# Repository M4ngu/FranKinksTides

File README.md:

# FranKinksTides
cc-by-sa original     design by Émile Gillet

https://www.tesseractmodular.com/eurorack-modules/frankinkstides-1-2

Dual Tidal Modulator - Eurorack Module

FranKinksTides is a eurorack module with 2 tidal modulators based on MI Tides1 (by Émilie Gillet) and the Swirls PCB layout  (by Electric Mist)

https://mutable-instruments.net/modules/tides1/

The central part is a mixer for the 2 signals and the Max/Min circuit from MI Kinks 

https://mutable-instruments.net/modules/kinks/

It can be a dual function generator, a complex oscillator or any other combination of VCO, LFO, ENV

version history:

## first version

-First working version of this kind of 'digital Maths'

## second version (v1.2):

-Mix output is now buffered, no signal bleeding on single outs.

-Mix pot controls also the balance of the signals sent to the max/min circuit.

-Uni/bi switch now also determines the signal sent to FM1.

-Clock/sync switch has now a center OFF position, no need of plugging a dummy cable in the Clock1 when using Sheeps firmware to avoid ultra fast sound bank changes. 

other small improvements for DIY:

-Bigger font size on the pcb.

-Parts renumbered for easy DIY.

## last version (v1.4):

-Added resistors to make the Balance pot exponential, so center position has a louder output.

-PCB modified with the Thonkiccon recommendation (with no ground plane / traces under the jacks)

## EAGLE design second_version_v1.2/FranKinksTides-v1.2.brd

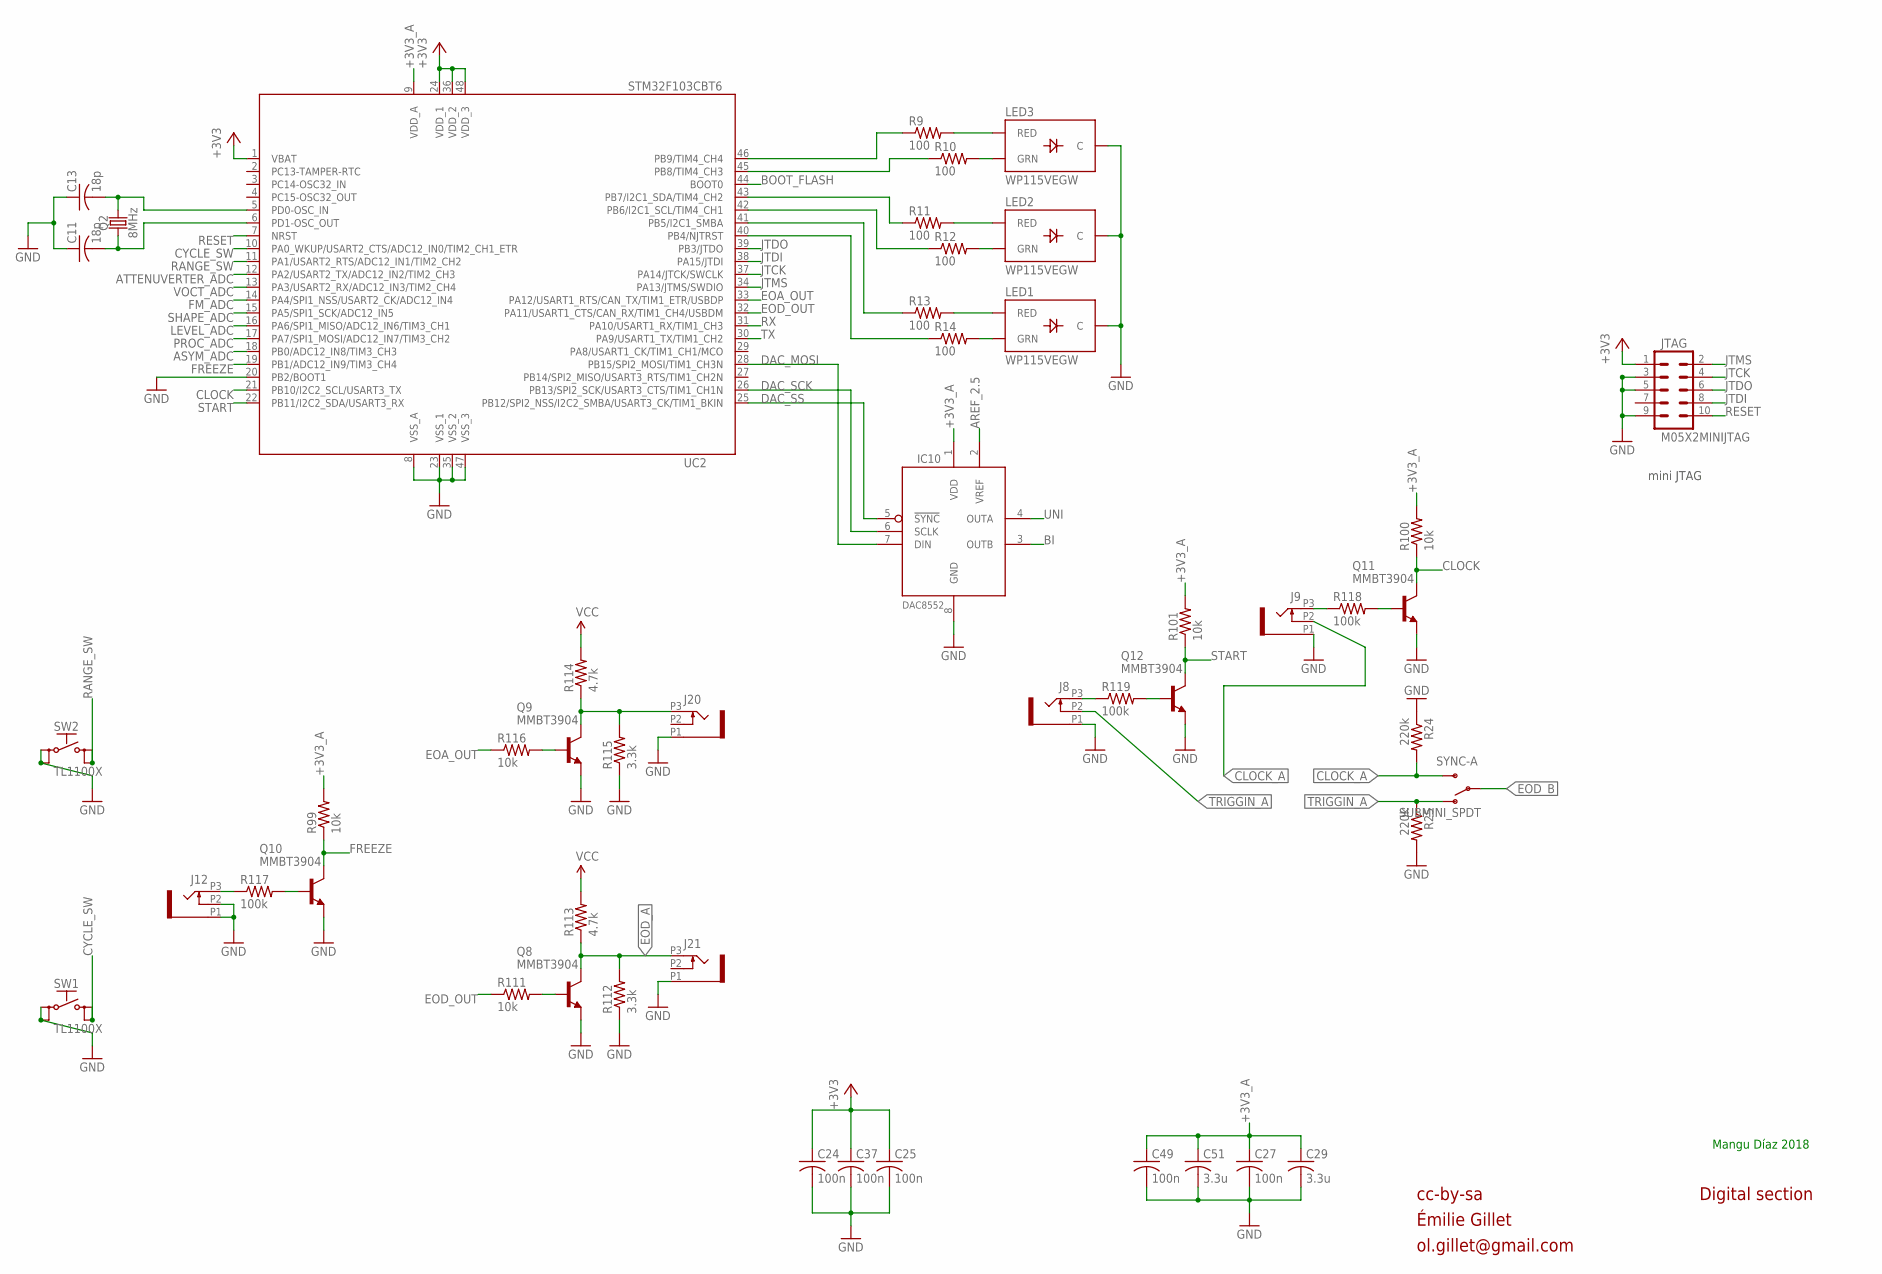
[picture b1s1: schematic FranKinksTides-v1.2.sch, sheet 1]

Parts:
C11, C13: 18p; C0603
C24, C25, C27, C37, C49: 100n; C0603
C29, C51: 3.3u; C0603
IC10: DAC8552; MSOP-8
J8, J9, J12, J20, J21: PJ301_GUI6; OG-PJ301_VARIATIONS_WQP_PJ_301M6
JTAG: M05X2MINIJTAG; 2X5-1.27
LED1, LED2, LED3: WP115VEGW; LED-BICOLOR-THROUGHHOLE
Q2: 8MHz; HC49UP
Q8, Q9, Q10, Q11, Q12: MMBT3904; SOT23-BEC
R9, R10, R11, R12, R13, R14: 100; R0603
R24, R25: 220k; R0603
R99, R100, R101, R111, R116: 10k; R0603
R112, R115: 3.3k; R0603
R113, R114: 4.7k; R0603
R117, R118, R119: 100k; R0603
SW1, SW2: TL1100X
SYNC-A: SUBMINI_SPDT; SUBMINI_TOGGLE
UC2: STM32F103CBT6; LQFP48

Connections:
+3V3: C24.1, C25.1, C37.1, JTAG.1, UC2.1 (VBAT), UC2.24 (VDD_1), UC2.36 (VDD_2), UC2.48 (VDD_3); also elsewhere on the board
+3V3_A: C27.1, C29.1, C49.1, C51.1, IC10.1 (VDD), R99.2, R100.2, R101.2, UC2.9 (VDD_A); also elsewhere on the board
AREF_2.5: IC10.2 (VREF); also elsewhere on the board
ASYM_ADC: UC2.18 (PB0/ADC12_IN8/TIM3_CH3); also elsewhere on the board
ATTENUVERTER_ADC: UC2.12 (PA2/USART2_TX/ADC12_IN2/TIM2_CH3); also elsewhere on the board
BI: IC10.3 (OUTB); also elsewhere on the board
BOOT_FLASH: UC2.44 (BOOT0); also elsewhere on the board
CLOCK: Q11.C, R100.1, UC2.21 (PB10/I2C2_SCL/USART3_TX); also elsewhere on the board
CLOCK_A: J9.P2 (2), R24.2, SYNC-A.3 (S)
CYCLE_SW: SW1.3 (S), SW1.4 (S1), UC2.10 (PA0_WKUP/USART2_CTS/ADC12_IN0/TIM2_CH1_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); also elsewhere on the board
DAC_MOSI: IC10.7 (DIN), UC2.28 (PB15/SPI2_MOSI/TIM1_CH3N); also elsewhere on the board
DAC_SCK: IC10.6 (SCLK), UC2.26 (PB13/SPI2_SCK/USART3_CTS/TIM1_CH1N); also elsewhere on the board
DAC_SS: IC10.5 (!SYNC), UC2.25 (PB12/SPI2_NSS/I2C2_SMBA/USART3_CK/TIM1_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); also elsewhere on the board
EOA_OUT: R116.1, UC2.33 (PA12/USART1_RTS/CAN_TX/TIM1_ETR/USBDP); also elsewhere on the board
EOD_A: J21.P3 (3), Q8.C, R112.2, R113.1; also elsewhere on the board
EOD_B: SYNC-A.COM (COMMON); also elsewhere on the board
EOD_OUT: R111.1, UC2.32 (PA11/USART1_CTS/CAN_RX/TIM1_CH4/USBDM); also elsewhere on the board
FM_ADC: UC2.14 (PA4/SPI1_NSS/USART2_CK/ADC12_IN4); also elsewhere on the board
FREEZE: Q10.C, R99.1, UC2.19 (PB1/ADC12_IN9/TIM3_CH4); also elsewhere on the board
GND: C11.1, C13.1, C24.2, C25.2, C27.2, C29.2, C37.2, C49.2, C51.2, IC10.8 (GND), J8.P1 (1), J9.P1 (1), J12.P1 (1), J12.P2 (2), J20.P1 (1), J21.P1 (1), JTAG.3, JTAG.5, JTAG.9, LED1.2 (C), LED2.2 (C), LED3.2 (C), Q8.E, Q9.E, Q10.E, Q11.E, Q12.E, R24.1, R25.2, R112.1, R115.1, SW1.1, SW1.2 (P1), SW2.1, SW2.2 (P1), UC2.8 (VSS_A), UC2.20 (PB2/BOOT1), UC2.23 (VSS_1), UC2.35 (VSS_2), UC2.47 (VSS_3); also elsewhere on the board
JTCK: JTAG.4, UC2.37 (PA14/JTCK/SWCLK); also elsewhere on the board
JTDI: JTAG.8, UC2.38 (PA15/JTDI); also elsewhere on the board
JTDO: JTAG.6, UC2.39 (PB3/JTDO); also elsewhere on the board
JTMS: JTAG.2, UC2.34 (PA13/JTMS/SWDIO); also elsewhere on the board
LEVEL_ADC: UC2.16 (PA6/SPI1_MISO/ADC12_IN6/TIM3_CH1); also elsewhere on the board
unnamed: C13.2, Q2.2, UC2.5 (PD0-OSC_IN)
unnamed: C11.2, Q2.1, UC2.6 (PD1-OSC_OUT)
unnamed: J8.P3 (3), R119.1
unnamed: J12.P3 (3), R117.1
unnamed: Q10.B, R117.2
unnamed: J9.P3 (3), R118.1
unnamed: Q11.B, R118.2
unnamed: Q8.B, R111.2
unnamed: LED3.3 (RED), R9.2
unnamed: LED3.1 (GRN), R10.2
unnamed: LED2.3 (RED), R11.2
unnamed: LED2.1 (GRN), R12.2
unnamed: LED1.3 (RED), R13.2
unnamed: LED1.1 (GRN), R14.2
unnamed: R9.1, UC2.46 (PB9/TIM4_CH4)
unnamed: R10.1, UC2.45 (PB8/TIM4_CH3)
unnamed: R11.1, UC2.43 (PB7/I2C1_SDA/TIM4_CH2)
unnamed: R12.1, UC2.42 (PB6/I2C1_SCL/TIM4_CH1)
unnamed: R13.1, UC2.41 (PB5/I2C1_SMBA)
unnamed: R14.1, UC2.40 (PB4/NJTRST)
unnamed: J20.P3 (3), Q9.C, R114.1, R115.2
unnamed: Q9.B, R116.2
unnamed: Q12.B, R119.2
PROC_ADC: UC2.17 (PA7/SPI1_MOSI/ADC12_IN7/TIM3_CH2); also elsewhere on the board
RANGE_SW: SW2.3 (S), SW2.4 (S1), UC2.11 (PA1/USART2_RTS/ADC12_IN1/TIM2_CH2); also elsewhere on the board
RESET: JTAG.10, UC2.7 (NRST); also elsewhere on the board
RX: UC2.31 (PA10/USART1_RX/TIM1_CH3); also elsewhere on the board
SHAPE_ADC: UC2.15 (PA5/SPI1_SCK/ADC12_IN5); also elsewhere on the board
START: Q12.C, R101.1, UC2.22 (PB11/I2C2_SDA/USART3_RX); also elsewhere on the board
TRIGGIN_A: J8.P2 (2), R25.1, SYNC-A.1 (O)
TX: UC2.30 (PA9/USART1_TX/TIM1_CH2); also elsewhere on the board
UNI: IC10.4 (OUTA); also elsewhere on the board
VCC: R113.2, R114.2; also elsewhere on the board
VOCT_ADC: UC2.13 (PA3/USART2_RX/ADC12_IN3/TIM2_CH4); also elsewhere on the board

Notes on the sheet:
cc-by-sa
Émilie Gillet
ol.gillet@gmail.com
Digital section
mini JTAG
Mangu Díaz 2018

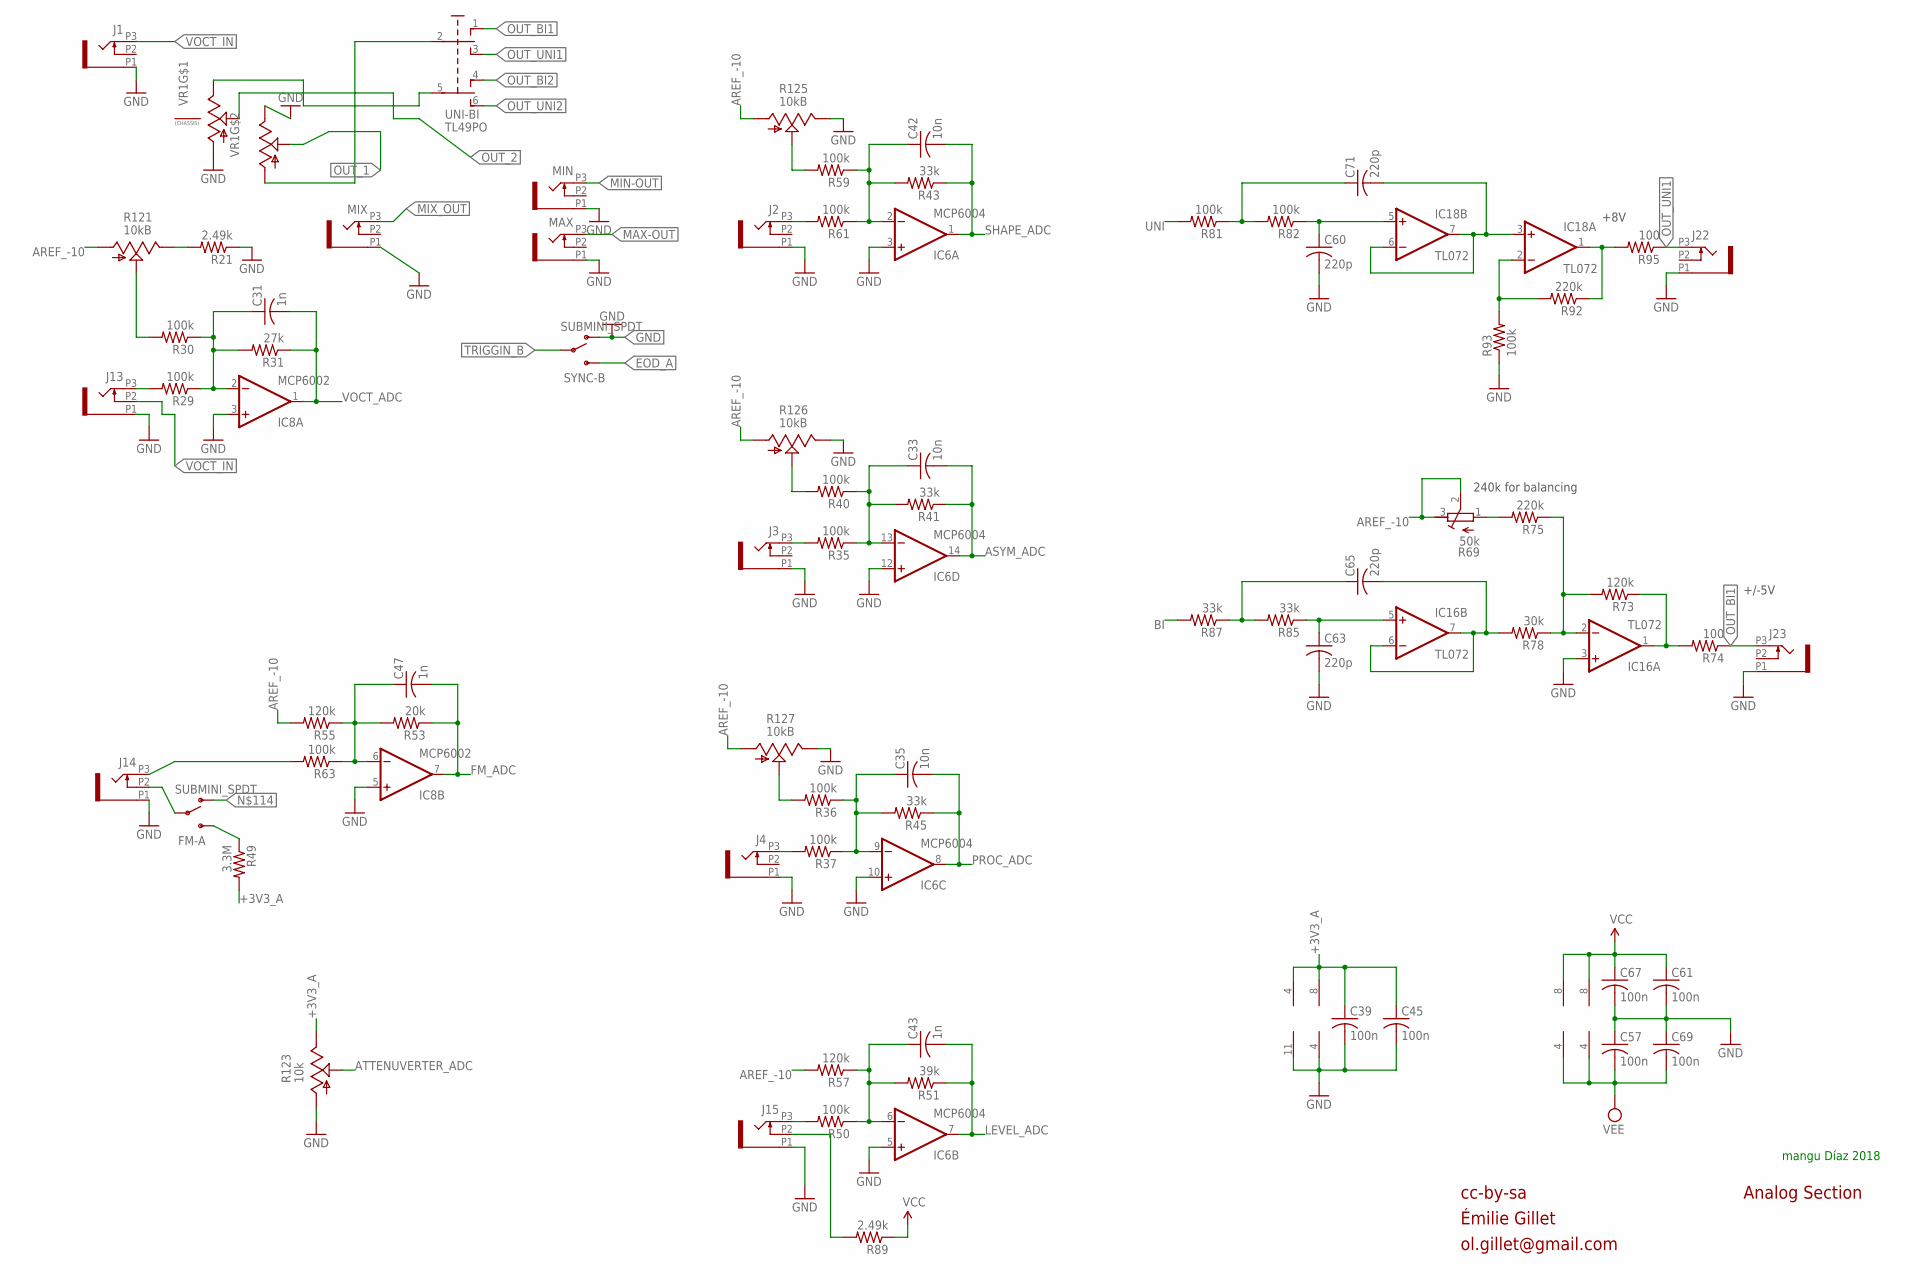
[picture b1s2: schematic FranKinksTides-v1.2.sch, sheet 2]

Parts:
C31, C43, C47: 1n; C0603
C33, C35, C42: 10n; C0603
C39, C45, C57, C61, C67, C69: 100n; C0603
C60, C63, C65, C71: 220p; C0603
FM-A: SUBMINI_SPDT; SUBMINI_TOGGLE
IC6: MCP6004; TSSOP14
IC8: MCP6002; SO08
IC16, IC18: TL072; TSSOP-8
J1, J2, J3, J4, J13, J14, J15, J22, J23: PJ301_GUI6; OG-PJ301_VARIATIONS_WQP_PJ_301M6
MAX: PJ301_GUI6; OG-PJ301_VARIATIONS_WQP_PJ_301M6
MIN: PJ301_GUI6; OG-PJ301_VARIATIONS_WQP_PJ_301M6
MIX: PJ301_GUI6; OG-PJ301_VARIATIONS_WQP_PJ_301M6
R21: 2.49k; R0603
R29, R30, R35, R36, R37, R40, R50, R59, R61, R63, R81, R82, R93: 100k; R0603
R31: 27k; R0603
R41, R43, R45, R85, R87: 33k; R0603
R49: 3.3M; R0603
R51: 39k; R0603
R53: 20k; R0603
R55, R57, R73: 120k; R0603
R69: 50k; RTRIM3296W
R74, R95: 100; R0603
R75, R92: 220k; R0603
R78: 30k; R0603
R89: 2.49k; R0805
R121: 10kB; ALPS_POT_VERTICAL_PS
R123: 10k; TALLTRIMMER
R125, R126, R127: 10kB; TALLTRIMMER
SYNC-B: SUBMINI_SPDT; SUBMINI_TOGGLE
UNI-BI: TL49PO; TL4XPO
VR1: ALPHA-9MM-DUALPOT; DUAL_9MM_SNAP-IN_POT

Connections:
+3V3_A: C39.1, C45.1, IC6.4 (V+), IC8.8 (V+), R49.2, R123.P$1 (E); also elsewhere on the board
AREF_-10: R55.2, R57.2, R69.2 (S), R69.3 (E), R121.P$3 (A), R125.P$3 (A), R126.P$3 (A), R127.P$3 (A); also elsewhere on the board
ASYM_ADC: C33.2, IC6.14 (OUT), R41.1; also elsewhere on the board
ATTENUVERTER_ADC: R123.P$2 (S); also elsewhere on the board
BI: R87.2; also elsewhere on the board
BI_OUT: IC16.1 (OUT), R73.1, R74.2
EOD_A: SYNC-B.3 (S); also elsewhere on the board
FM_ADC: C47.2, IC8.7 (OUT), R53.1; also elsewhere on the board
F_CV: IC16.2 (-IN), R73.2, R75.1, R78.1
GND: C39.2, C45.2, C57.1, C60.2, C61.2, C63.2, C67.2, C69.1, IC6.3 (+IN), IC6.5 (+IN), IC6.10 (+IN), IC6.11 (V-), IC6.12 (+IN), IC8.3 (+IN), IC8.4 (V-), IC8.5 (+IN), IC16.3 (+IN), J1.P1 (1), J2.P1 (1), J3.P1 (1), J4.P1 (1), J13.P1 (1), J14.P1 (1), J15.P1 (1), J22.P1 (1), J23.P1 (1), MAX.P1 (1), MIN.P1 (1), MIX.P1 (1), R21.1, R93.1, R123.P$3 (A), R125.P$1 (E), R126.P$1 (E), R127.P$1 (E), SYNC-B.1 (O), VR1.1 (A), VR1.3B (E); also elsewhere on the board
LEVEL_ADC: C43.2, IC6.7 (OUT), R51.1; also elsewhere on the board
MAX-OUT: MAX.P3 (3); also elsewhere on the board
MIN-OUT: MIN.P3 (3); also elsewhere on the board
MIX_OUT: MIX.P3 (3); also elsewhere on the board
unnamed: J2.P3 (3), R61.2
unnamed: C42.1, IC6.2 (-IN), R43.2, R59.1, R61.1
unnamed: R59.2, R125.P$2 (S)
unnamed: J3.P3 (3), R35.2
unnamed: C33.1, IC6.13 (-IN), R35.1, R40.1, R41.2
unnamed: FM-A.3 (S), R49.1
unnamed: R40.2, R126.P$2 (S)
unnamed: J4.P3 (3), R37.2
unnamed: C35.1, IC6.9 (-IN), R36.1, R37.1, R45.2
unnamed: R36.2, R127.P$2 (S)
unnamed: J15.P3 (3), R50.2
unnamed: C43.1, IC6.6 (-IN), R50.1, R51.2, R57.1
unnamed: J13.P3 (3), R29.2
unnamed: C31.1, IC8.2 (-IN), R29.1, R30.1, R31.2
unnamed: R30.2, R121.P$2 (S)
unnamed: R21.2, R121.P$1 (E)
unnamed: J14.P3 (3), R63.2
unnamed: C47.1, IC8.6 (-IN), R53.2, R55.1, R63.1
unnamed: FM-A.COM (COMMON), J14.P2 (2)
unnamed: R69.1 (A), R75.2
unnamed: IC18.2 (-IN), R92.2, R93.2
unnamed: C65.2, IC16.6 (-IN), IC16.7 (OUT), R78.2
unnamed: C63.1, IC16.5 (+IN), R85.1
unnamed: C65.1, R85.2, R87.1
unnamed: IC18.1 (OUT), R92.1, R95.2
unnamed: J15.P2 (2), R89.2
unnamed: C71.2, IC18.3 (+IN), IC18.6 (-IN), IC18.7 (OUT)
unnamed: C60.1, IC18.5 (+IN), R82.1
unnamed: C71.1, R81.1, R82.2
unnamed: FM-A.1 (O), UNI-BI.5 (P1), VR1.3 (E)
unnamed: UNI-BI.2, VR1.1B (A)
OUT_1: VR1.2B (S); also elsewhere on the board
OUT_2: VR1.2 (S); also elsewhere on the board
OUT_BI1: J23.P3 (3), R74.1, UNI-BI.1 (O)
OUT_BI2: UNI-BI.4 (O1); also elsewhere on the board
OUT_UNI1: J22.P3 (3), R95.1, UNI-BI.3 (S)
OUT_UNI2: UNI-BI.6 (S1); also elsewhere on the board
PROC_ADC: C35.2, IC6.8 (OUT), R45.1; also elsewhere on the board
SHAPE_ADC: C42.2, IC6.1 (OUT), R43.1; also elsewhere on the board
TRIGGIN_B: SYNC-B.COM (COMMON); also elsewhere on the board
UNI: R81.2; also elsewhere on the board
VCC: C61.1, C67.1, IC16.8 (V+), IC18.8 (V+), R89.1; also elsewhere on the board
VEE: C57.2, C69.2, IC16.4 (V-), IC18.4 (V-); also elsewhere on the board
VOCT_ADC: C31.2, IC8.1 (OUT), R31.1; also elsewhere on the board
VOCT_IN: J1.P3 (3), J13.P2 (2); also elsewhere on the board

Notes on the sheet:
cc-by-sa
Émilie Gillet
ol.gillet@gmail.com
Analog Section
+8V
+/-5V
240k for balancing
mangu Díaz 2018

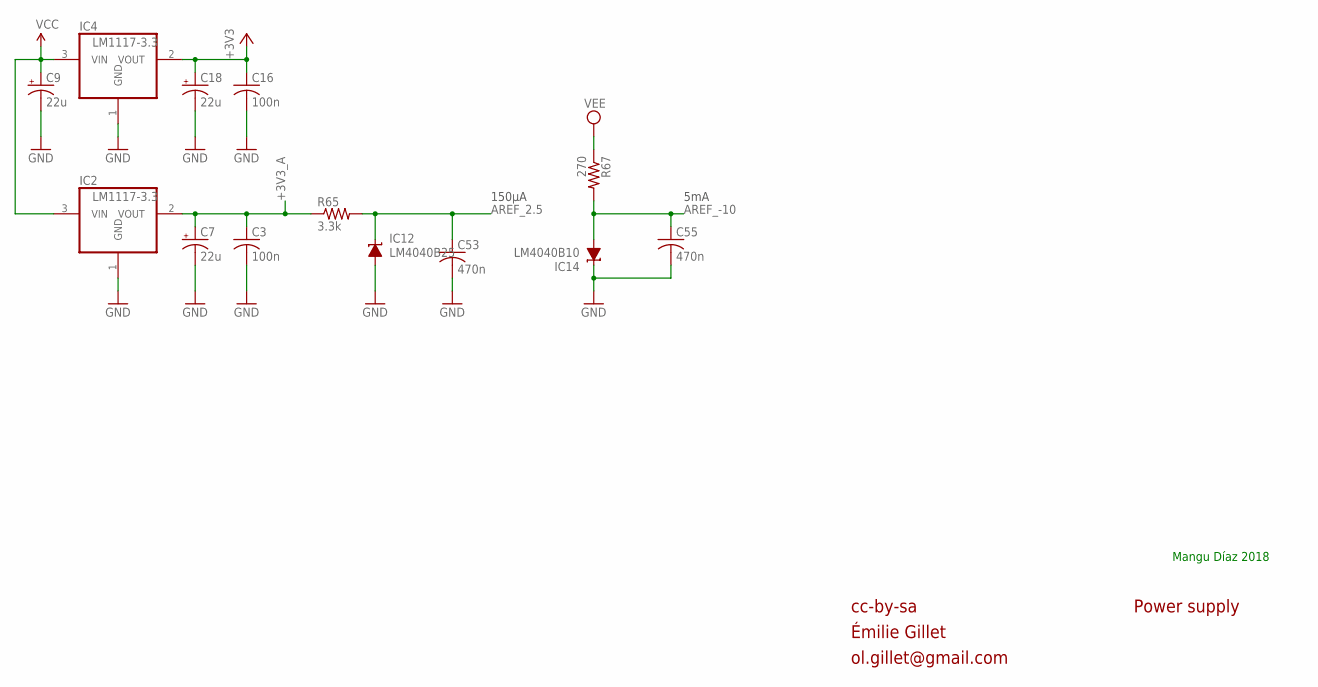
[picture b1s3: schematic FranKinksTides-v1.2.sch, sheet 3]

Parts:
C3, C16: 100n; C0603
C7, C9, C18: 22u; PANASONIC_C
C53, C55: 470n; C0603
IC2, IC4: LM1117-3.3; SOT223
IC12: LM4040B25; DBZ_R-PDSO-G3
IC14: LM4040B10; DBZ_R-PDSO-G3
R65: 3.3k; R0603
R67: 270; R0603

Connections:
+3V3: C16.1, C18.+, IC4.2 (VOUT); also elsewhere on the board
+3V3_A: C3.1, C7.+, IC2.2 (VOUT), R65.1; also elsewhere on the board
AREF_2.5: C53.1, IC12.1 (C), R65.2; also elsewhere on the board
AREF_-10: C55.1, IC14.2 (A), R67.2; also elsewhere on the board
GND: C3.2, C7.-, C9.-, C16.2, C18.-, C53.2, C55.2, IC2.1 (GND), IC4.1 (GND), IC12.2 (A), IC14.1 (C); also elsewhere on the board
VCC: C9.+, IC2.3 (VIN), IC4.3 (VIN); also elsewhere on the board
VEE: R67.1; also elsewhere on the board

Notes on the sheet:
cc-by-sa
Émilie Gillet
ol.gillet@gmail.com
Power supply
5mA
150µA
Mangu Díaz 2018

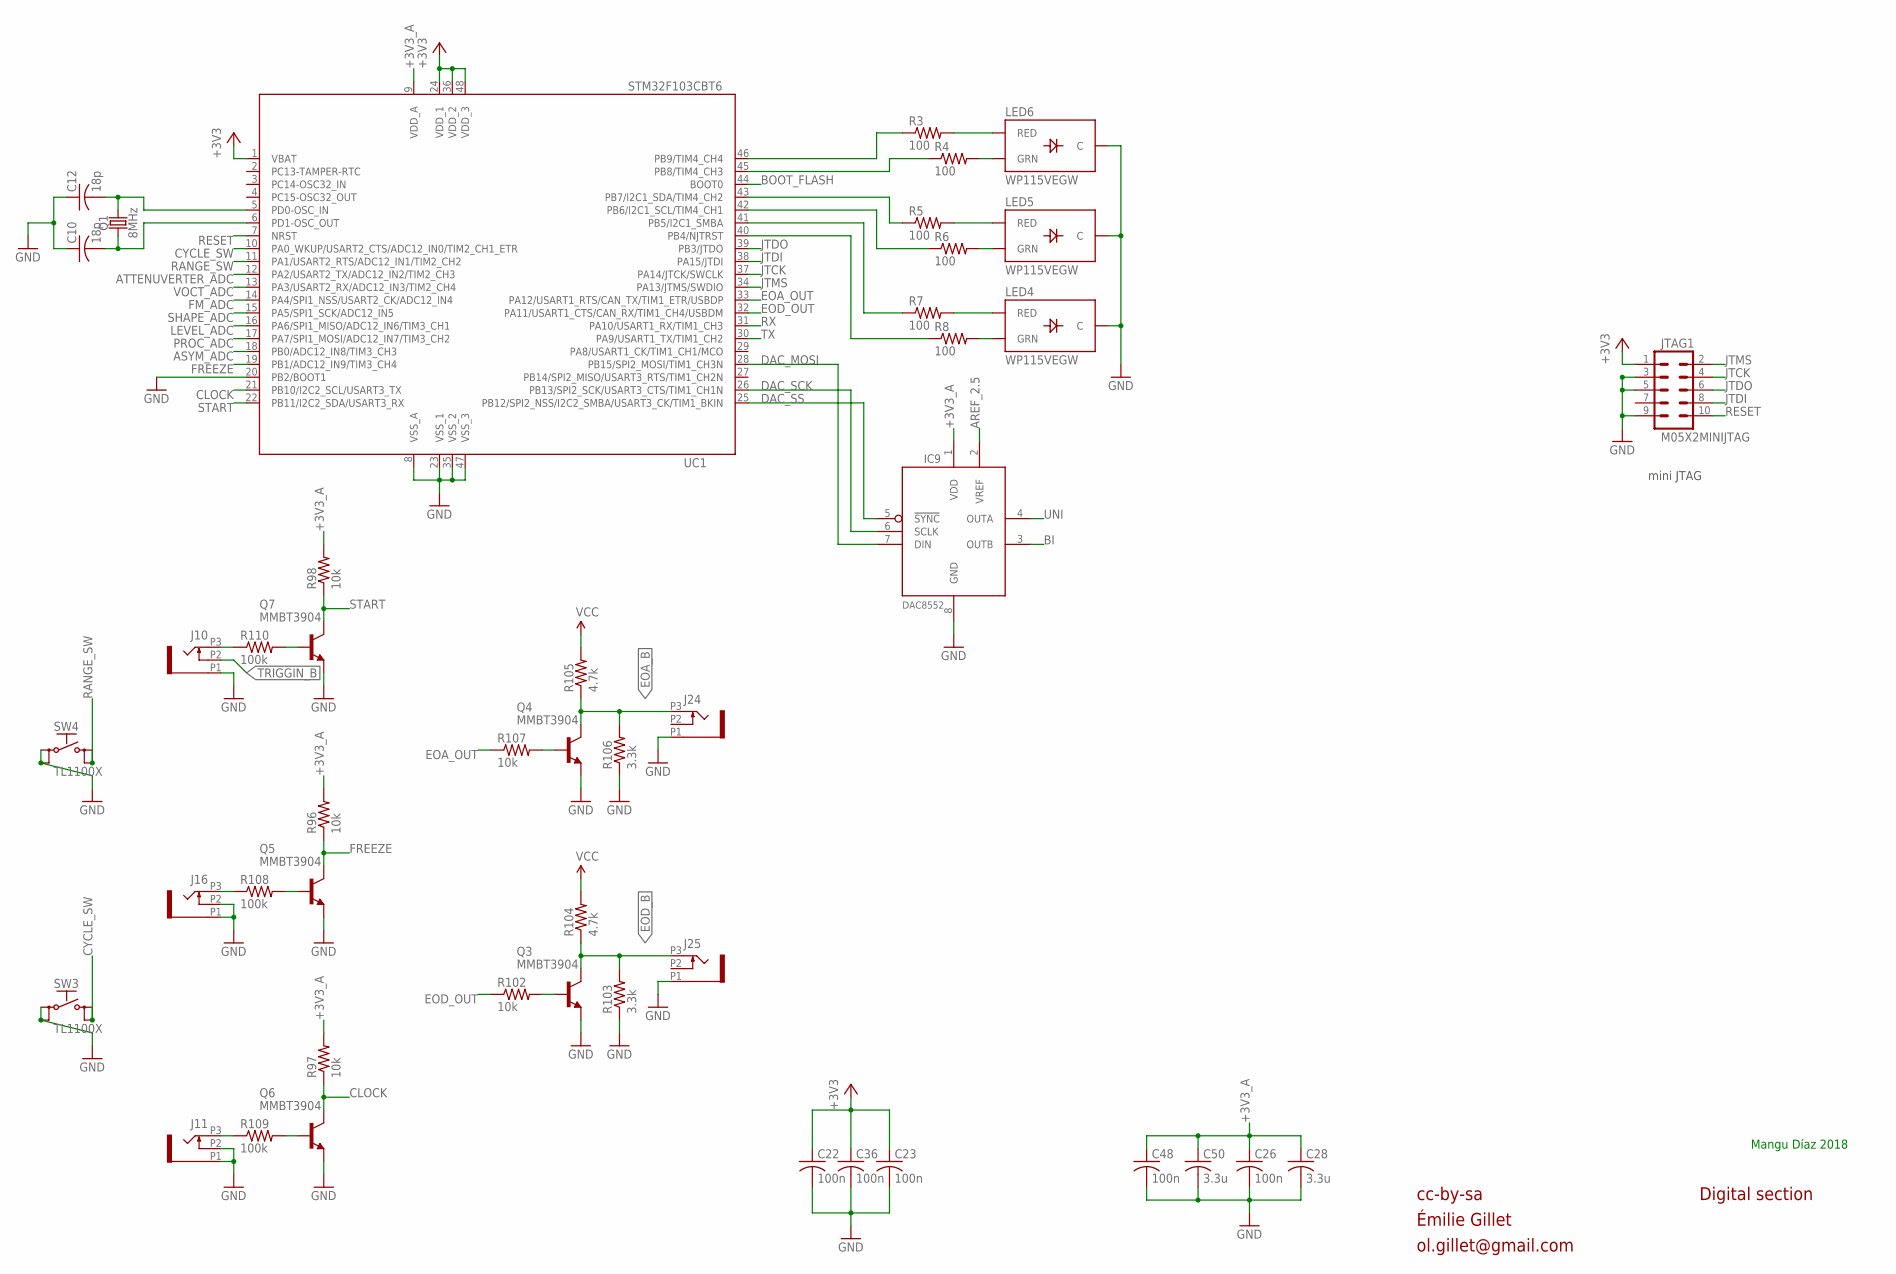
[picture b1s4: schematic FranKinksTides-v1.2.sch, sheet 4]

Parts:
C10, C12: 18p; C0603
C22, C23, C26, C36, C48: 100n; C0603
C28, C50: 3.3u; C0603
IC9: DAC8552; MSOP-8
J10, J11, J16, J24, J25: PJ301_GUI6; OG-PJ301_VARIATIONS_WQP_PJ_301M6
JTAG1: M05X2MINIJTAG; 2X5-1.27
LED4, LED5, LED6: WP115VEGW; LED-BICOLOR-THROUGHHOLE
Q1: 8MHz; HC49UP
Q3, Q4, Q5, Q6, Q7: MMBT3904; SOT23-BEC
R3, R4, R5, R6, R7, R8: 100; R0603
R96, R97, R98, R102, R107: 10k; R0603
R103, R106: 3.3k; R0603
R104, R105: 4.7k; R0603
R108, R109, R110: 100k; R0603
SW3, SW4: TL1100X
UC1: STM32F103CBT6; LQFP48

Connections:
+3V3: C22.1, C23.1, C36.1, JTAG1.1, UC1.1 (VBAT), UC1.24 (VDD_1), UC1.36 (VDD_2), UC1.48 (VDD_3); also elsewhere on the board
+3V3_A: C26.1, C28.1, C48.1, C50.1, IC9.1 (VDD), R96.2, R97.2, R98.2, UC1.9 (VDD_A); also elsewhere on the board
AREF_2.5: IC9.2 (VREF); also elsewhere on the board
ASYM_ADC: UC1.18 (PB0/ADC12_IN8/TIM3_CH3); also elsewhere on the board
ATTENUVERTER_ADC: UC1.12 (PA2/USART2_TX/ADC12_IN2/TIM2_CH3); also elsewhere on the board
BI: IC9.3 (OUTB); also elsewhere on the board
BOOT_FLASH: UC1.44 (BOOT0); also elsewhere on the board
CLOCK: Q6.C, R97.1, UC1.21 (PB10/I2C2_SCL/USART3_TX); also elsewhere on the board
CYCLE_SW: SW3.3 (S), SW3.4 (S1), UC1.10 (PA0_WKUP/USART2_CTS/ADC12_IN0/TIM2_CH1_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); also elsewhere on the board
DAC_MOSI: IC9.7 (DIN), UC1.28 (PB15/SPI2_MOSI/TIM1_CH3N); also elsewhere on the board
DAC_SCK: IC9.6 (SCLK), UC1.26 (PB13/SPI2_SCK/USART3_CTS/TIM1_CH1N); also elsewhere on the board
DAC_SS: IC9.5 (!SYNC), UC1.25 (PB12/SPI2_NSS/I2C2_SMBA/USART3_CK/TIM1_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); also elsewhere on the board
EOA_B: J24.P3 (3), Q4.C, R105.1, R106.2
EOA_OUT: R107.1, UC1.33 (PA12/USART1_RTS/CAN_TX/TIM1_ETR/USBDP); also elsewhere on the board
EOD_B: J25.P3 (3), Q3.C, R103.2, R104.1; also elsewhere on the board
EOD_OUT: R102.1, UC1.32 (PA11/USART1_CTS/CAN_RX/TIM1_CH4/USBDM); also elsewhere on the board
FM_ADC: UC1.14 (PA4/SPI1_NSS/USART2_CK/ADC12_IN4); also elsewhere on the board
FREEZE: Q5.C, R96.1, UC1.19 (PB1/ADC12_IN9/TIM3_CH4); also elsewhere on the board
GND: C10.1, C12.1, C22.2, C23.2, C26.2, C28.2, C36.2, C48.2, C50.2, IC9.8 (GND), J10.P1 (1), J11.P1 (1), J11.P2 (2), J16.P1 (1), J16.P2 (2), J24.P1 (1), J25.P1 (1), JTAG1.3, JTAG1.5, JTAG1.9, LED4.2 (C), LED5.2 (C), LED6.2 (C), Q3.E, Q4.E, Q5.E, Q6.E, Q7.E, R103.1, R106.1, SW3.1, SW3.2 (P1), SW4.1, SW4.2 (P1), UC1.8 (VSS_A), UC1.20 (PB2/BOOT1), UC1.23 (VSS_1), UC1.35 (VSS_2), UC1.47 (VSS_3); also elsewhere on the board
JTCK: JTAG1.4, UC1.37 (PA14/JTCK/SWCLK); also elsewhere on the board
JTDI: JTAG1.8, UC1.38 (PA15/JTDI); also elsewhere on the board
JTDO: JTAG1.6, UC1.39 (PB3/JTDO); also elsewhere on the board
JTMS: JTAG1.2, UC1.34 (PA13/JTMS/SWDIO); also elsewhere on the board
LEVEL_ADC: UC1.16 (PA6/SPI1_MISO/ADC12_IN6/TIM3_CH1); also elsewhere on the board
unnamed: C12.2, Q1.2, UC1.5 (PD0-OSC_IN)
unnamed: C10.2, Q1.1, UC1.6 (PD1-OSC_OUT)
unnamed: Q4.B, R107.2
unnamed: Q3.B, R102.2
unnamed: LED6.3 (RED), R3.2
unnamed: LED6.1 (GRN), R4.2
unnamed: LED5.3 (RED), R5.2
unnamed: LED5.1 (GRN), R6.2
unnamed: LED4.3 (RED), R7.2
unnamed: LED4.1 (GRN), R8.2
unnamed: R3.1, UC1.46 (PB9/TIM4_CH4)
unnamed: R4.1, UC1.45 (PB8/TIM4_CH3)
unnamed: R5.1, UC1.43 (PB7/I2C1_SDA/TIM4_CH2)
unnamed: R6.1, UC1.42 (PB6/I2C1_SCL/TIM4_CH1)
unnamed: R7.1, UC1.41 (PB5/I2C1_SMBA)
unnamed: R8.1, UC1.40 (PB4/NJTRST)
unnamed: J10.P3 (3), R110.1
unnamed: Q7.B, R110.2
unnamed: J16.P3 (3), R108.1
unnamed: Q5.B, R108.2
unnamed: J11.P3 (3), R109.1
unnamed: Q6.B, R109.2
PROC_ADC: UC1.17 (PA7/SPI1_MOSI/ADC12_IN7/TIM3_CH2); also elsewhere on the board
RANGE_SW: SW4.3 (S), SW4.4 (S1), UC1.11 (PA1/USART2_RTS/ADC12_IN1/TIM2_CH2); also elsewhere on the board
RESET: JTAG1.10, UC1.7 (NRST); also elsewhere on the board
RX: UC1.31 (PA10/USART1_RX/TIM1_CH3); also elsewhere on the board
SHAPE_ADC: UC1.15 (PA5/SPI1_SCK/ADC12_IN5); also elsewhere on the board
START: Q7.C, R98.1, UC1.22 (PB11/I2C2_SDA/USART3_RX); also elsewhere on the board
TRIGGIN_B: J10.P2 (2); also elsewhere on the board
TX: UC1.30 (PA9/USART1_TX/TIM1_CH2); also elsewhere on the board
UNI: IC9.4 (OUTA); also elsewhere on the board
VCC: R104.2, R105.2; also elsewhere on the board
VOCT_ADC: UC1.13 (PA3/USART2_RX/ADC12_IN3/TIM2_CH4); also elsewhere on the board

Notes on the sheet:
cc-by-sa
Émilie Gillet
ol.gillet@gmail.com
Digital section
mini JTAG
Mangu Díaz 2018

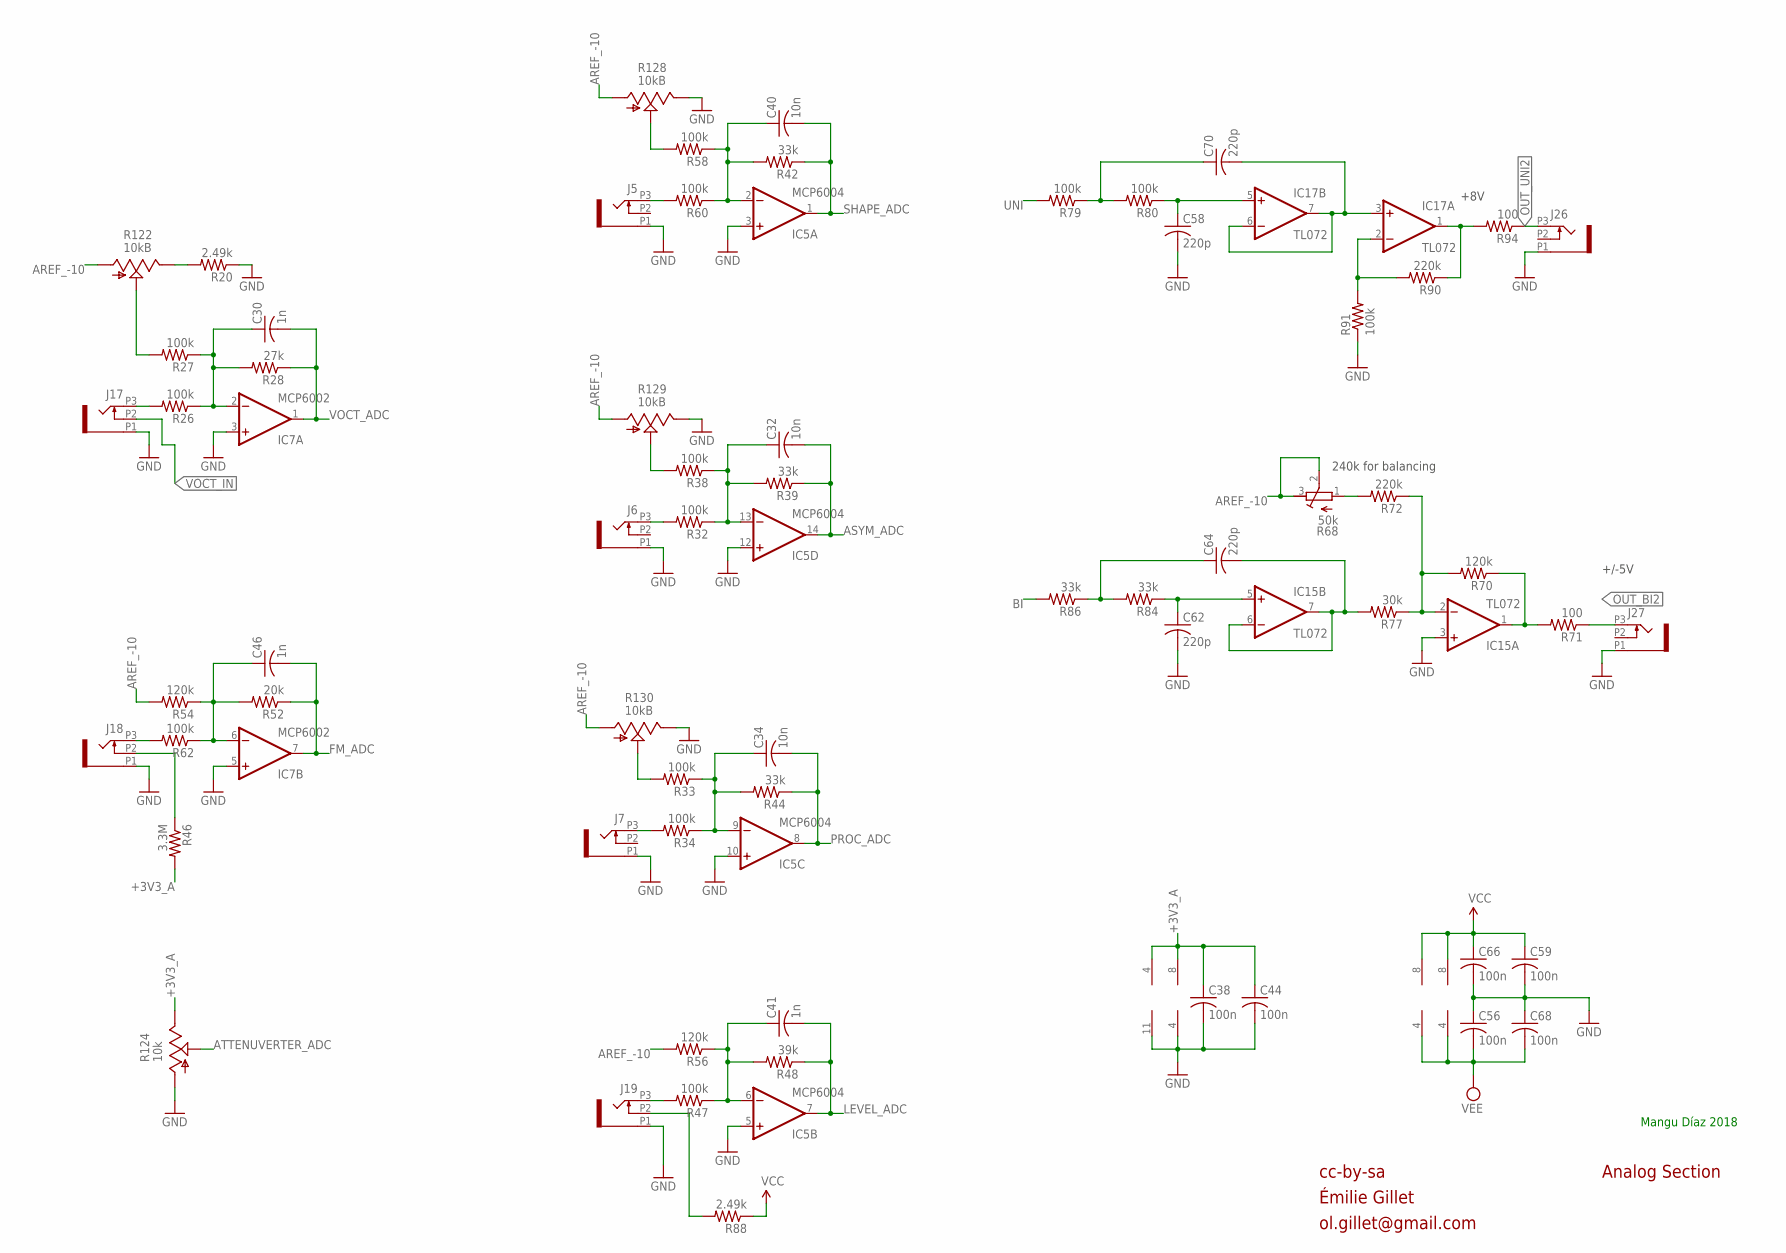
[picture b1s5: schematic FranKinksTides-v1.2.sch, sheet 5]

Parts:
C30, C41, C46: 1n; C0603
C32, C34, C40: 10n; C0603
C38, C44, C56, C59, C66, C68: 100n; C0603
C58, C62, C64, C70: 220p; C0603
IC5: MCP6004; TSSOP14
IC7: MCP6002; SO08
IC15, IC17: TL072; TSSOP-8
J5, J6, J7, J17, J18, J19, J26, J27: PJ301_GUI6; OG-PJ301_VARIATIONS_WQP_PJ_301M6
R20: 2.49k; R0603
R26, R27, R32, R33, R34, R38, R47, R58, R60, R62, R79, R80, R91: 100k; R0603
R28: 27k; R0603
R39, R42, R44, R84, R86: 33k; R0603
R46: 3.3M; R0603
R48: 39k; R0603
R52: 20k; R0603
R54, R56, R70: 120k; R0603
R68: 50k; RTRIM3296W
R71, R94: 100; R0603
R72, R90: 220k; R0603
R77: 30k; R0603
R88: 2.49k; R0805
R122: 10kB; ALPS_POT_VERTICAL_PS
R124: 10k; TALLTRIMMER
R128, R129, R130: 10kB; TALLTRIMMER

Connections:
+3V3_A: C38.1, C44.1, IC5.4 (V+), IC7.8 (V+), R46.2, R124.P$1 (E); also elsewhere on the board
AREF_-10: R54.2, R56.2, R68.2 (S), R68.3 (E), R122.P$3 (A), R128.P$3 (A), R129.P$3 (A), R130.P$3 (A); also elsewhere on the board
ASYM_ADC: C32.2, IC5.14 (OUT), R39.1; also elsewhere on the board
ATTENUVERTER_ADC: R124.P$2 (S); also elsewhere on the board
BI: R86.2; also elsewhere on the board
BI_OUT1: IC15.1 (OUT), R70.1, R71.2
FM_ADC: C46.2, IC7.7 (OUT), R52.1; also elsewhere on the board
F_CV1: IC15.2 (-IN), R70.2, R72.1, R77.1
GND: C38.2, C44.2, C56.1, C58.2, C59.2, C62.2, C66.2, C68.1, IC5.3 (+IN), IC5.5 (+IN), IC5.10 (+IN), IC5.11 (V-), IC5.12 (+IN), IC7.3 (+IN), IC7.4 (V-), IC7.5 (+IN), IC15.3 (+IN), J5.P1 (1), J6.P1 (1), J7.P1 (1), J17.P1 (1), J18.P1 (1), J19.P1 (1), J26.P1 (1), J27.P1 (1), R20.1, R91.1, R124.P$3 (A), R128.P$1 (E), R129.P$1 (E), R130.P$1 (E); also elsewhere on the board
LEVEL_ADC: C41.2, IC5.7 (OUT), R48.1; also elsewhere on the board
unnamed: J5.P3 (3), R60.2
unnamed: C40.1, IC5.2 (-IN), R42.2, R58.1, R60.1
unnamed: R58.2, R128.P$2 (S)
unnamed: J6.P3 (3), R32.2
unnamed: C32.1, IC5.13 (-IN), R32.1, R38.1, R39.2
unnamed: R38.2, R129.P$2 (S)
unnamed: J7.P3 (3), R34.2
unnamed: C34.1, IC5.9 (-IN), R33.1, R34.1, R44.2
unnamed: R33.2, R130.P$2 (S)
unnamed: J19.P3 (3), R47.2
unnamed: C41.1, IC5.6 (-IN), R47.1, R48.2, R56.1
unnamed: J17.P3 (3), R26.2
unnamed: C30.1, IC7.2 (-IN), R26.1, R27.1, R28.2
unnamed: R27.2, R122.P$2 (S)
unnamed: R20.2, R122.P$1 (E)
unnamed: J18.P3 (3), R62.2
unnamed: C46.1, IC7.6 (-IN), R52.2, R54.1, R62.1
unnamed: C70.2, IC17.3 (+IN), IC17.6 (-IN), IC17.7 (OUT)
unnamed: C58.1, IC17.5 (+IN), R80.1
unnamed: C70.1, R79.1, R80.2
unnamed: IC17.2 (-IN), R90.2, R91.2
unnamed: C64.2, IC15.6 (-IN), IC15.7 (OUT), R77.2
unnamed: C62.1, IC15.5 (+IN), R84.1
unnamed: C64.1, R84.2, R86.1
unnamed: J18.P2 (2), R46.1
unnamed: IC17.1 (OUT), R90.1, R94.2
unnamed: R68.1 (A), R72.2
unnamed: J19.P2 (2), R88.2
OUT_BI2: J27.P3 (3), R71.1; also elsewhere on the board
OUT_UNI2: J26.P3 (3), R94.1; also elsewhere on the board
PROC_ADC: C34.2, IC5.8 (OUT), R44.1; also elsewhere on the board
SHAPE_ADC: C40.2, IC5.1 (OUT), R42.1; also elsewhere on the board
UNI: R79.2; also elsewhere on the board
VCC: C59.1, C66.1, IC15.8 (V+), IC17.8 (V+), R88.1; also elsewhere on the board
VEE: C56.2, C68.2, IC15.4 (V-), IC17.4 (V-); also elsewhere on the board
VOCT_ADC: C30.2, IC7.1 (OUT), R28.1; also elsewhere on the board
VOCT_IN: J17.P2 (2); also elsewhere on the board

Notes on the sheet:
cc-by-sa
Émilie Gillet
ol.gillet@gmail.com
Analog Section
+8V
+/-5V
240k for balancing
Mangu Díaz 2018

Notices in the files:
second_version_v1.2/FranKinksTides-v1.2.brd:
Original design Émilie  Gillet cc-by-sa
parts and their libraries:
switch-e-switch: Copyright (C) 2010, Bob Starr
SparkFun-Clocks: Licensing: Creative Commons ShareAlike 4.0 International - https://creativecommons.org/licenses/by-sa/4.0
